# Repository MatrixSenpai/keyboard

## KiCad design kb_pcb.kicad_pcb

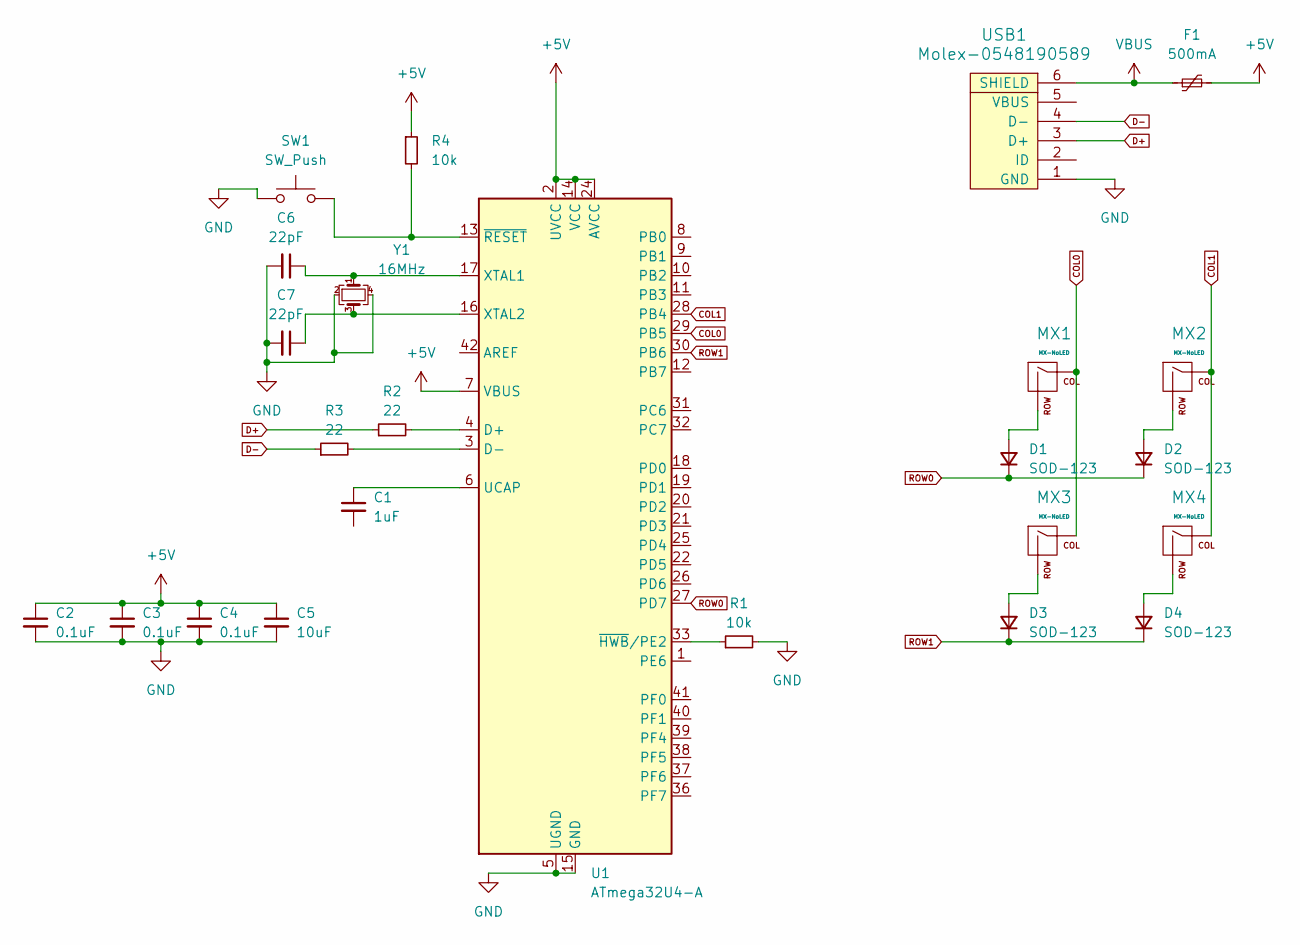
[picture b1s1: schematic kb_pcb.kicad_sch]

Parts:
C1: 1uF; C_0805_2012Metric
C2, C3, C4: 0.1uF; C_0805_2012Metric
C5: 10uF; C_0805_2012Metric
C6, C7: 22pF; C_0805_2012Metric
D1, D2, D3, D4: SOD-123; D_SOD-123
F1: 500mA; Fuse_1206_3216Metric
MX1, MX2, MX3, MX4: MX-NoLED; MX-1U-NoLED
R1, R4: 10k; R_0805_2012Metric
R2, R3: 22; R_0805_2012Metric
SW1: SW_Push; Reset_Pretty
U1: ATmega32U4-A; TQFP-44_10x10mm_P0.8mm
USB1: Molex-0548190589
Y1: 16MHz; Crystal_SMD_3225-4Pin_3.2x2.5mm

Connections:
+5V: C2.1, C3.1, C4.1, C5.1, F1.2, R4.1, U1.2 (UVCC), U1.7 (VBUS), U1.14 (VCC), U1.24 (AVCC), U1.34 (VCC), U1.44 (AVCC)
COL0: MX1.1 (COL), MX3.1 (COL), U1.29 (PB5)
COL1: MX2.1 (COL), MX4.1 (COL), U1.28 (PB4)
D+: R2.1, USB1.3 (D+)
D-: R3.1, USB1.4 (D-)
GND: C2.2, C3.2, C4.2, C5.2, C6.2, C7.2, R1.2, SW1.1, U1.5 (UGND), U1.15 (GND), U1.23 (GND), U1.35 (GND), U1.43 (GND), USB1.1 (GND), Y1.2, Y1.4
unnamed: D1.2 (A), MX1.2 (ROW)
unnamed: D2.2 (A), MX2.2 (ROW)
unnamed: D3.2 (A), MX3.2 (ROW)
unnamed: D4.2 (A), MX4.2 (ROW)
unnamed: R2.2, U1.4 (D+)
unnamed: R3.2, U1.3 (D-)
unnamed: C1.1, U1.6 (UCAP)
unnamed: C6.1, U1.17 (XTAL1), Y1.1
unnamed: C7.1, U1.16 (XTAL2), Y1.3
unnamed: R1.1, U1.33 (~HWB/PE2)
unnamed: R4.2, SW1.2, U1.13 (~RESET)
ROW0: D1.1 (K), D2.1 (K), U1.27 (PD7)
ROW1: D3.1 (K), D4.1 (K), U1.30 (PB6)
VBUS: F1.1, USB1.6 (SHIELD)

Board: 2 copper layers, 24 parts (4 on the bottom side), 20 nets, no tracks yet.

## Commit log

2023-06-10 adding submodules
2023-06-10 libraries
2023-06-11 pcb basic design
2023-06-11 layout stuff
2023-06-15 schematic initial design
